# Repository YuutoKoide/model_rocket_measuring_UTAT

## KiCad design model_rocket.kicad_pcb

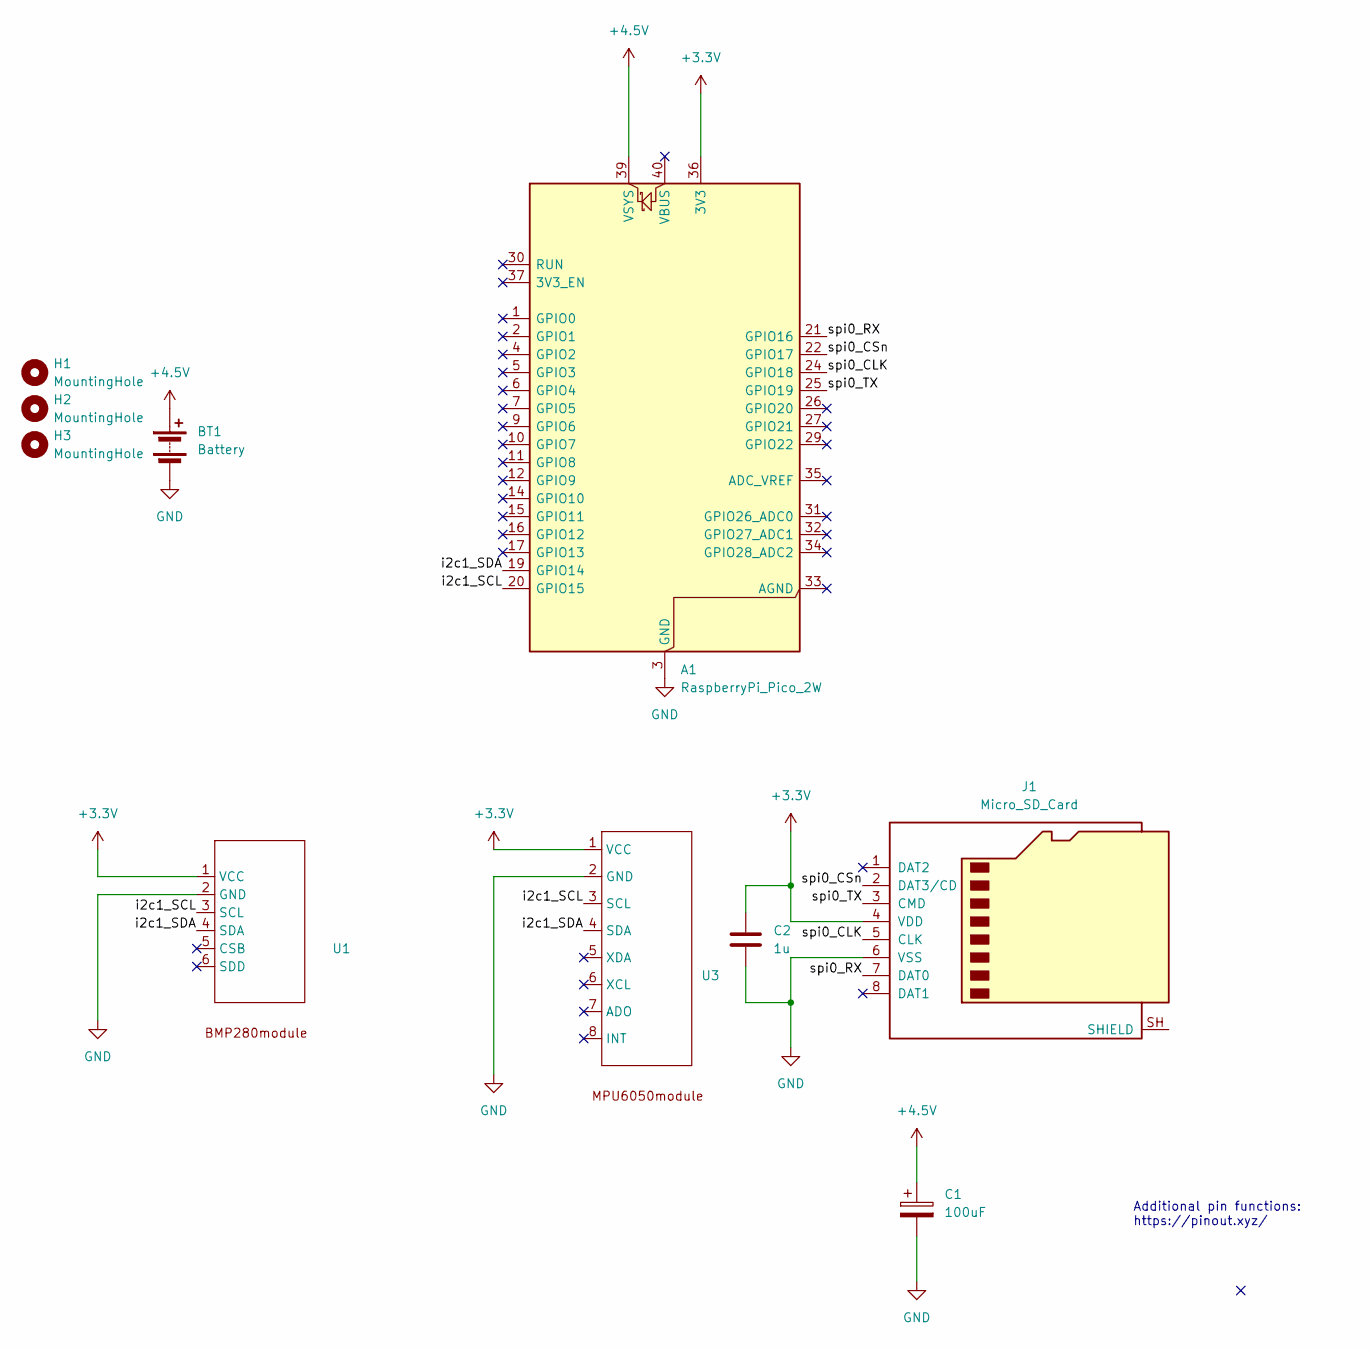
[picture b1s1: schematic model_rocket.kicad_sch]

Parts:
A1: RaspberryPi_Pico_2W; RaspberryPi_Pico_Common_Unspecified
BT1: Battery; BatteryHolder_MPD_BC2AAPC_2xAA
C1: 100uF; CP_Radial_D5.0mm_P2.00mm
C2: 1u; C_Disc_D5.0mm_W2.5mm_P2.50mm
H1, H2, H3: MountingHole; MountingHole_3.2mm_M3
J1: Micro_SD_Card; PinHeader_1x08_P2.54mm_Vertical
U1: PinHeader_1x06_P2.54mm_Vertical
U3: PinHeader_1x08_P2.54mm_Vertical

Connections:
+3.3V: A1.36 (3V3), C2.1, J1.4 (VDD), U1.1 (VCC), U3.1 (VCC)
+4.5V: A1.39 (VSYS), BT1.1 (+), C1.1
/i2c1_SCL: A1.20 (GPIO15), U1.3 (SCL), U3.3 (SCL)
/i2c1_SDA: A1.19 (GPIO14), U1.4 (SDA), U3.4 (SDA)
/spi0_CLK: A1.24 (GPIO18), J1.5 (CLK)
/spi0_CSn: A1.22 (GPIO17), J1.2 (DAT3/CD)
/spi0_RX: A1.21 (GPIO16), J1.7 (DAT0)
/spi0_TX: A1.25 (GPIO19), J1.3 (CMD)
GND: A1.3 (GND), A1.8 (GND), A1.13 (GND), A1.18 (GND), A1.23 (GND), A1.28 (GND), A1.38 (GND), BT1.2 (-), C1.2, C2.2, J1.6 (VSS), U1.2 (GND), U3.2 (GND)

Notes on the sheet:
Additional pin functions: https://pinout.xyz/

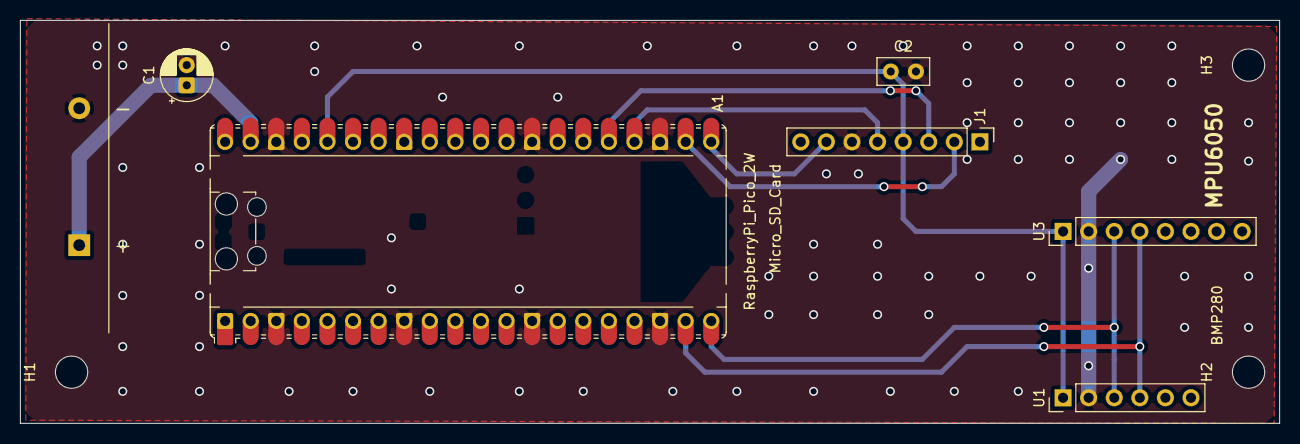
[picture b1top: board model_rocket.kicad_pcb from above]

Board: 2 copper layers, 125.0 x 40.0 mm, 14 parts (0 on the bottom side), 9 nets.

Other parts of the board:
MH1, MH2, MH3, MH4: MountingHole_2.7mm_M2.5
